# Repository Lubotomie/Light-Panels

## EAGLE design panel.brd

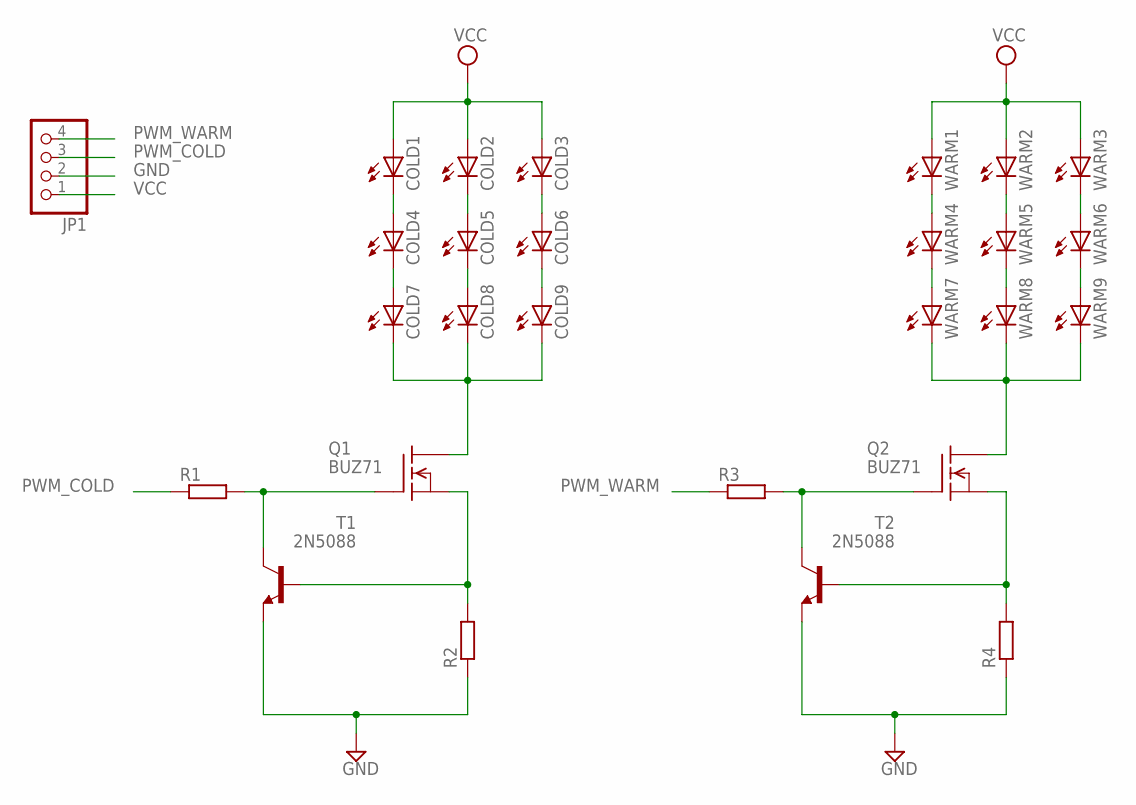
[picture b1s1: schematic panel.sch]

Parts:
COLD1, COLD2, COLD3, COLD4, COLD5, COLD6, COLD7, COLD8, COLD9: LEDP-LCC-2; P-LCC-2
JP1: PINHD-1X4; 1X04
Q1, Q2: BUZ71; TO220
R1, R2, R3, R4: R-EU_0207/10; 0207/10
T1, T2: 2N5088; TO92
WARM1, WARM2, WARM3, WARM4, WARM5, WARM6, WARM7, WARM8, WARM9: LEDP-LCC-2; P-LCC-2

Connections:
GND: JP1.2, R2.1, R4.1, T1.3 (E), T2.3 (E)
unnamed: COLD1.C, COLD4.A
unnamed: COLD4.C, COLD7.A
unnamed: COLD2.C, COLD5.A
unnamed: COLD5.C, COLD8.A
unnamed: COLD3.C, COLD6.A
unnamed: COLD6.C, COLD9.A
unnamed: COLD7.C, COLD8.C, COLD9.C, Q1.2 (D)
unnamed: Q1.3 (S), R2.2, T1.2 (B)
unnamed: WARM1.C, WARM4.A
unnamed: Q1.1 (G), R1.2, T1.1 (C)
unnamed: WARM4.C, WARM7.A
unnamed: WARM2.C, WARM5.A
unnamed: WARM5.C, WARM8.A
unnamed: WARM3.C, WARM6.A
unnamed: Q2.2 (D), WARM7.C, WARM8.C, WARM9.C
unnamed: Q2.3 (S), R4.2, T2.2 (B)
unnamed: Q2.1 (G), R3.2, T2.1 (C)
PWM_COLD: JP1.3, R1.1
PWM_WARM: JP1.4, R3.1
VCC: COLD1.A, COLD2.A, COLD3.A, JP1.1, WARM1.A, WARM2.A, WARM3.A
WARM6: WARM6.C, WARM9.A

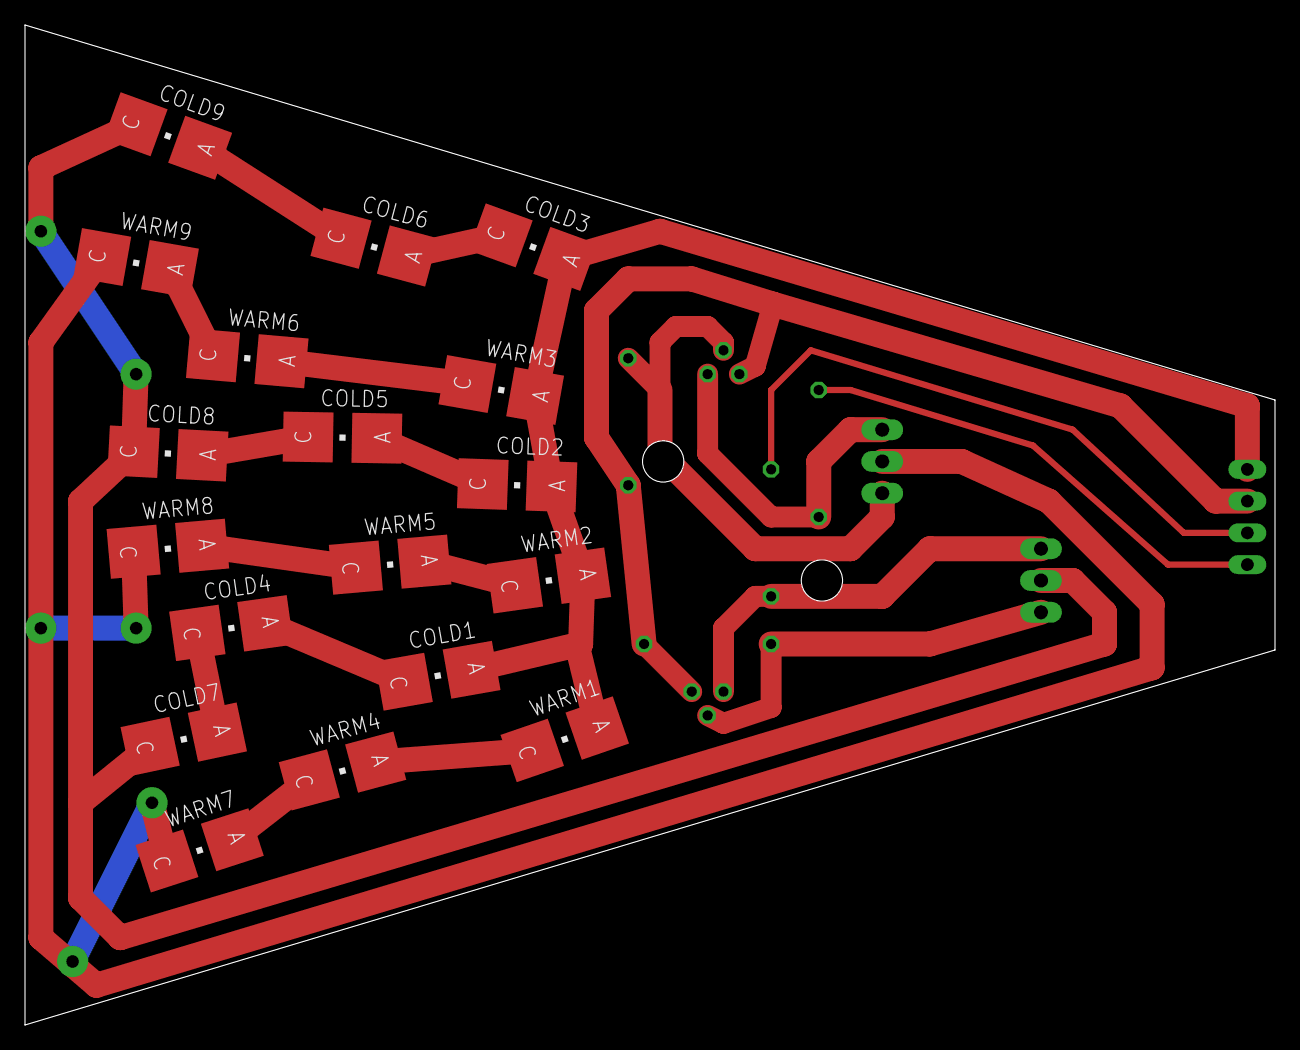
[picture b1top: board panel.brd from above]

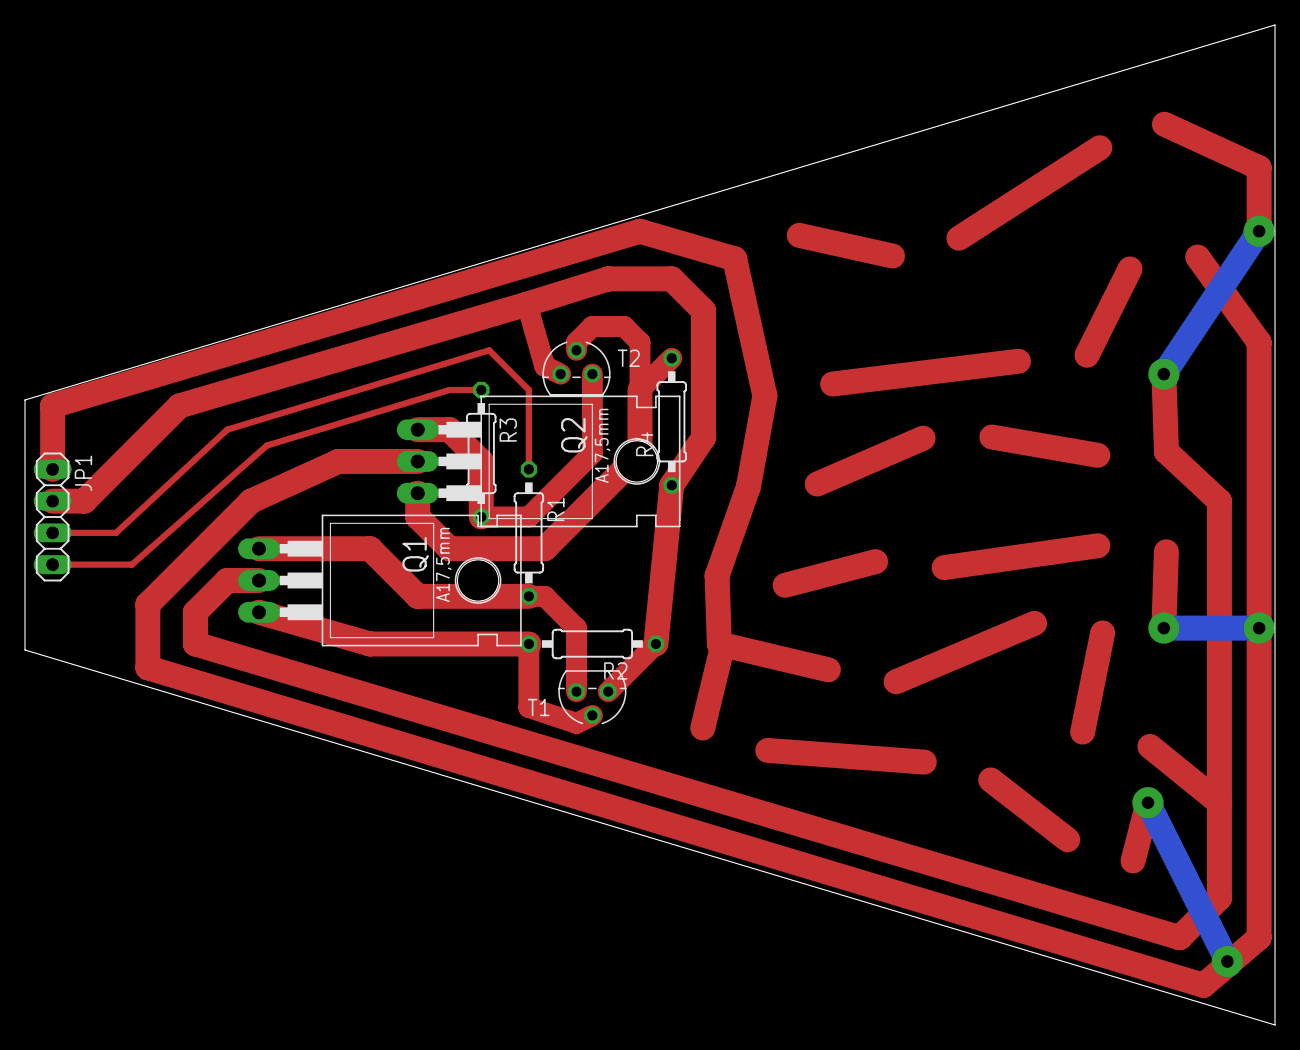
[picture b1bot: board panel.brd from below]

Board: 2 copper layers, 100.0 x 80.0 mm, 27 parts (9 on the bottom side), 22 nets.
